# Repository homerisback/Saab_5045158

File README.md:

# Saab 5045158
Fan regulator mainboard/PCB to replace *SAAB 9-3 1998-2003* faulty regulator at reasonnable costs. #36 on diagram below

Due to high heating functioning tempreature, main MOSFET on board ends in failing. Board/soldering pads may be damaged as well as components.

This is made to replace PCB and its components, you need to take back from original SAAB part #5045158 :
  - wiring and connector
  - housing and screws
  - vertical plate on PCB<br>
  
## Build and use this at your own risks.<br>High intensity involved that may lead to fire if not properly build<br>**Check twice** there are no shortcuts or badly soldered components.<br>

Inital intention was to replace faulty part but after a close magnified look that showed the damage, I ended to make a complete 1:1 copy of original board layout under Eagle CAD.<br>
Schematic & board design files are available up here.

Ordering PCB is doable at [OSHPark](https://oshpark.com/projects/qXP4BEkH/view_design) (**note that they sell boards by sets of 3 minimum**)<br>

Here is a BOM to order parts - *I ordered at Mouser's, that's why I left their ref in table below*  
(***note that some parts are SMD - be sure to have ability and tools to solder them***)

| N° Mouser :          | N° de fab. :       | Desc. :                                                   | Client ref. | Qty |
|----------------------|--------------------|-----------------------------------------------------------|-------------|-----|
| 844-IRFP054PBF       | IRFP054PBF         | MOSFET TO247 N CHANNEL 60V                                | VT1         | 1   |
| 512-BC547B           | BC547B             | BJT NPN Epitaxial Silicon Transistor                      | VT2         | 1   |
| 603-MF0204FTE52-3K16 | MF0204FTE52-3K16   | Through hole 3.16Kohms 1% 1/8watt                         | R13         | 1   |
| 594-5063JD10K50F     | MBA02040C1052FC100 | Through hole 10.5Kohms 1% 1/8watt body size               | R11         | 1   |
| 71-CMF5078K700FHEB   | CMF5078K700FHEB    | Through hole 1/4watt 78.7Kohms 1%                         | R14         | 1   |
| 71-MBA02040C2200FCT0 | MBA02040C2200FCT00 | Through hole 1/4watt 220ohm 1% 50ppm                      | R8-9        | 2   |
| 594-5063JD6K200FT    | MBA02040C6201FRP00 | Through hole 6.2Kohms 1% 1/8watt body size                | R3,R7       | 2   |
| 594-5063JD2K200F5    | MBA02040C2201FCT00 | Through hole 2.2Kohms 1% 1/8watt body size                | R1-2        | 2   |
| 594-5063JD1K000FT    | MBA02040C1001FRP00 | Through hole 1Kohms 1% 1/8watt body size                  | R15         | 1   |
| 594-5063JD10K1%TR    | MBA02040C1002FRP00 | Through hole 10Kohms 1% 1/8watt body size                 | R4,R12      | 2   |
| 594-5063JD100K0F5    | MBA02040C1003FCT00 | Through hole 100Kohms 1% 1/8watt body size                | R5          | 1   |
| 595-LM2904BTQDRQ1    | LM2904BTQDRQ1      | Amplis-Op Automotive-grade du al 36-V 1.2-MHz op          | U1          | 1   |
| 594-5063JD18K70F     | MBA02040C1872FC100 | Through hole 18.7Kohms 1% 1/8watt body size               | R6          | 1   |
| 603-AC0805JNPO9BN181 | AC0805JRNPO9BN181  | MLCC - CMS 50 V 180pF C0G 0805 5%                         | C4, C6-11   | 7   |
| 810-FA14C0G2A103JNU6 | FA14C0G2A103JNU06  | Through hole MLCC 100V 0.01uF C0G 5% RAD LS:2.5mm         | C1          | 1   |
| 810-FA28X8R1H104KRU6 | FA28X8R1H104KRU06  | Through hole MLCC 50V 0.1uF X8R 10% RAD LS:5mm            | C2-3,C5     | 3   |
| 621-1N4007           | 1N4007-T           | Diode Vr/1000V Io/1A T/R                                  | D1          | 1   |
<br>
<br>
<br>

# Work done !
<details>
  
  <summary>Have a look at the brand new board</summary>
  
Here's the new board soldered and ready to mount in car and enjoy a working fan  

</details>

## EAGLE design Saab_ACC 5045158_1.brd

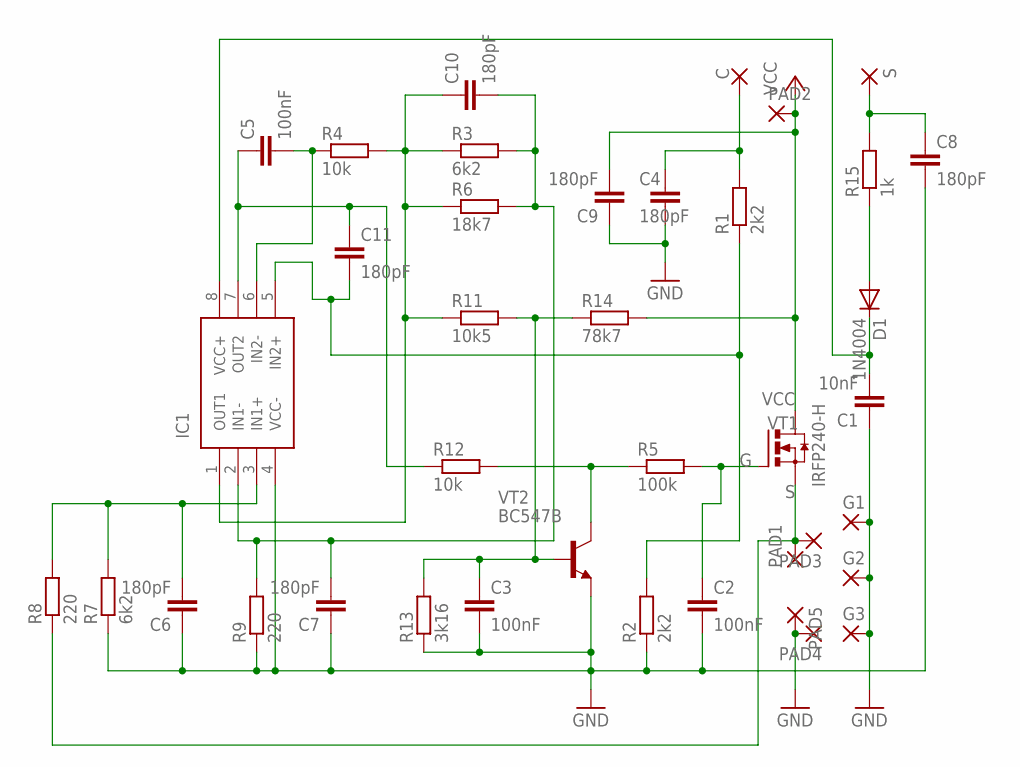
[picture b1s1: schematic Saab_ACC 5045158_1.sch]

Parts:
C: 3,17/1,3
C1: 10nF; C2.5-2
C2, C3, C5: 100nF; C050-024X044
C4, C6, C7, C8, C9, C10, C11: 180pF; C0805K
D1: 1N4004; DO41-10
G1: 3,81/1,4
G2, G3: 3,17/1,3
IC1: LM2904YDT; SOIC127P600X175-8N
PAD1, PAD3, PAD4, PAD5: SMD5; SMD2,54-5,08
PAD2: 3,81/1,4
R1, R2: 2k2; 0204/5
R3, R7: 6k2; 0204/5
R4, R12: 10k; 0204/5
R5: 100k; 0204/5
R6: 18k7; 0207/10
R8, R9: 220; 0204/5
R11: 10k5; 0204/7
R13: 3k16; 0204/7
R14: 78k7; 0204/7
R15: 1k; 0204/5
S: 3,17/1,3
VT1: IRFP240-H; TO247BH
VT2: BC547B; TO92

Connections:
C: C.1, C4.1, R1.2
G: C2.1, R5.2, VT1.G
GND: C1.1, C2.2, C3.2, C4.2, C6.1, C7.1, C8.2, C9.1, G1.1, G2.1, G3.1, IC1.4 (VCC-), PAD4.1, PAD5.1, R2.1, R7.1, R9.1, R13.1, VT2.1 (E)
unnamed: R5.1, R12.2, VT2.3 (C)
unnamed: C5.1, C11.1, IC1.7 (OUT2), R12.1
unnamed: C5.2, IC1.6 (IN2-), R4.1
unnamed: C10.1, IC1.1 (OUT1), R3.1, R4.2, R6.1, R11.1
unnamed: C7.2, C10.2, IC1.2 (IN1-), R3.2, R6.2, R9.2
unnamed: C3.1, R11.2, R13.2, R14.1, VT2.2 (B)
unnamed: C11.2, IC1.5 (IN2+), R1.1, R2.2
unnamed: C6.2, IC1.3 (IN1+), R7.2, R8.2
unnamed: C8.1, R15.2, S.1
unnamed: D1.A, R15.1
unnamed: C1.2, D1.C, IC1.8 (VCC+)
S: PAD1.1, PAD3.1, R8.1, VT1.S
VCC: C9.2, PAD2.1, R14.2, VT1.D

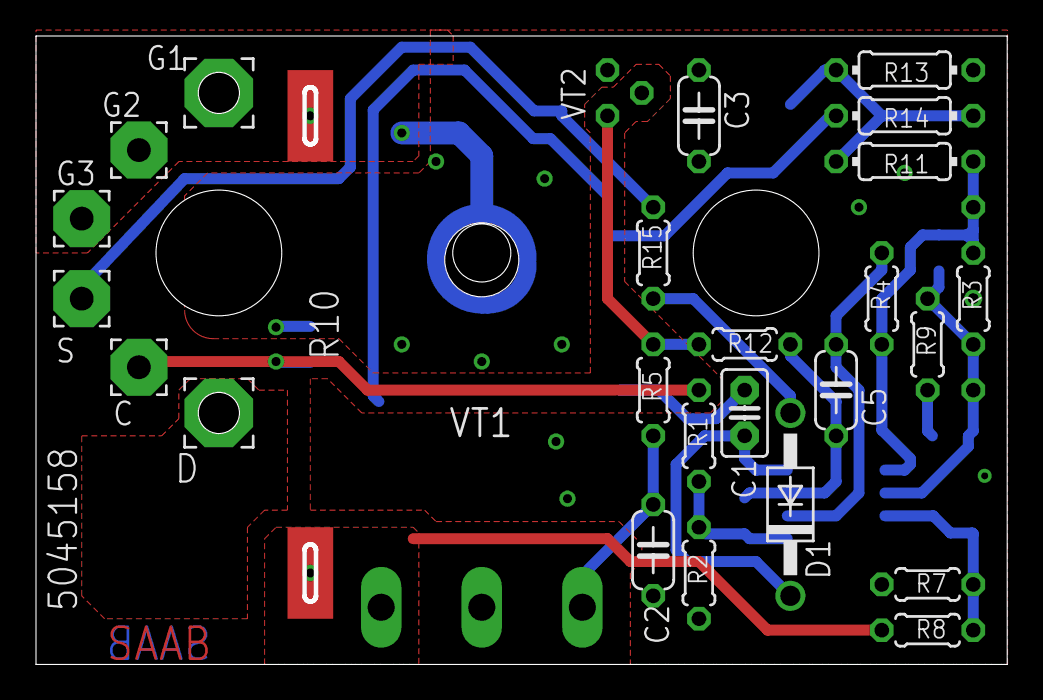
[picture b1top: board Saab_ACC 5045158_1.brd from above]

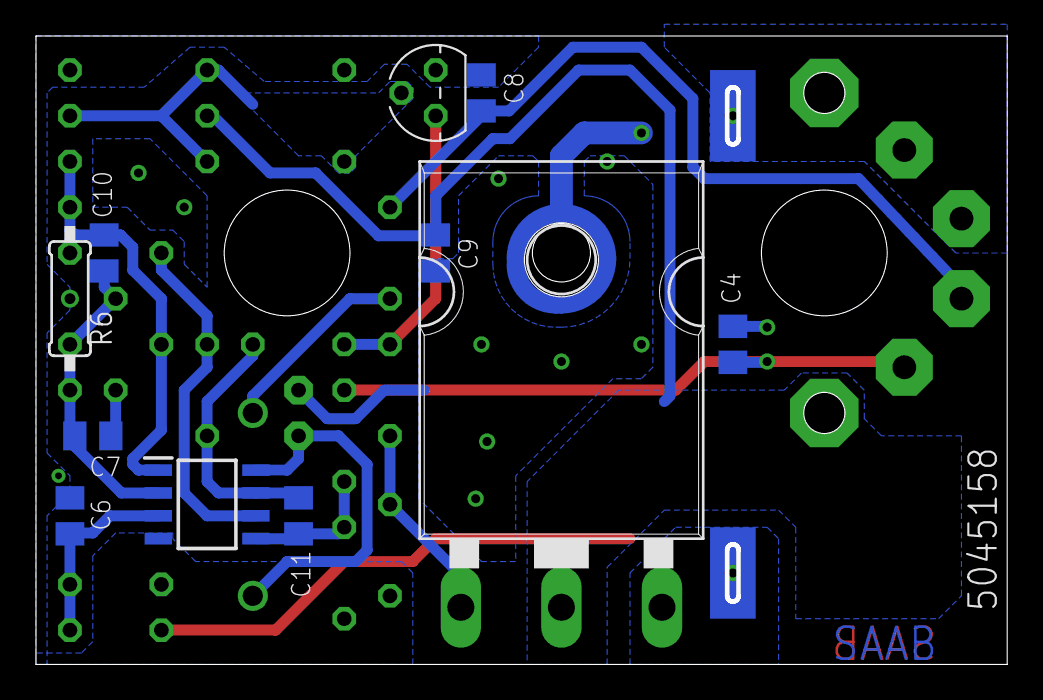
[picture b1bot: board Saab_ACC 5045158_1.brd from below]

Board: 2 copper layers, 53.7 x 34.7 mm, 39 parts (13 on the bottom side), 16 nets.
